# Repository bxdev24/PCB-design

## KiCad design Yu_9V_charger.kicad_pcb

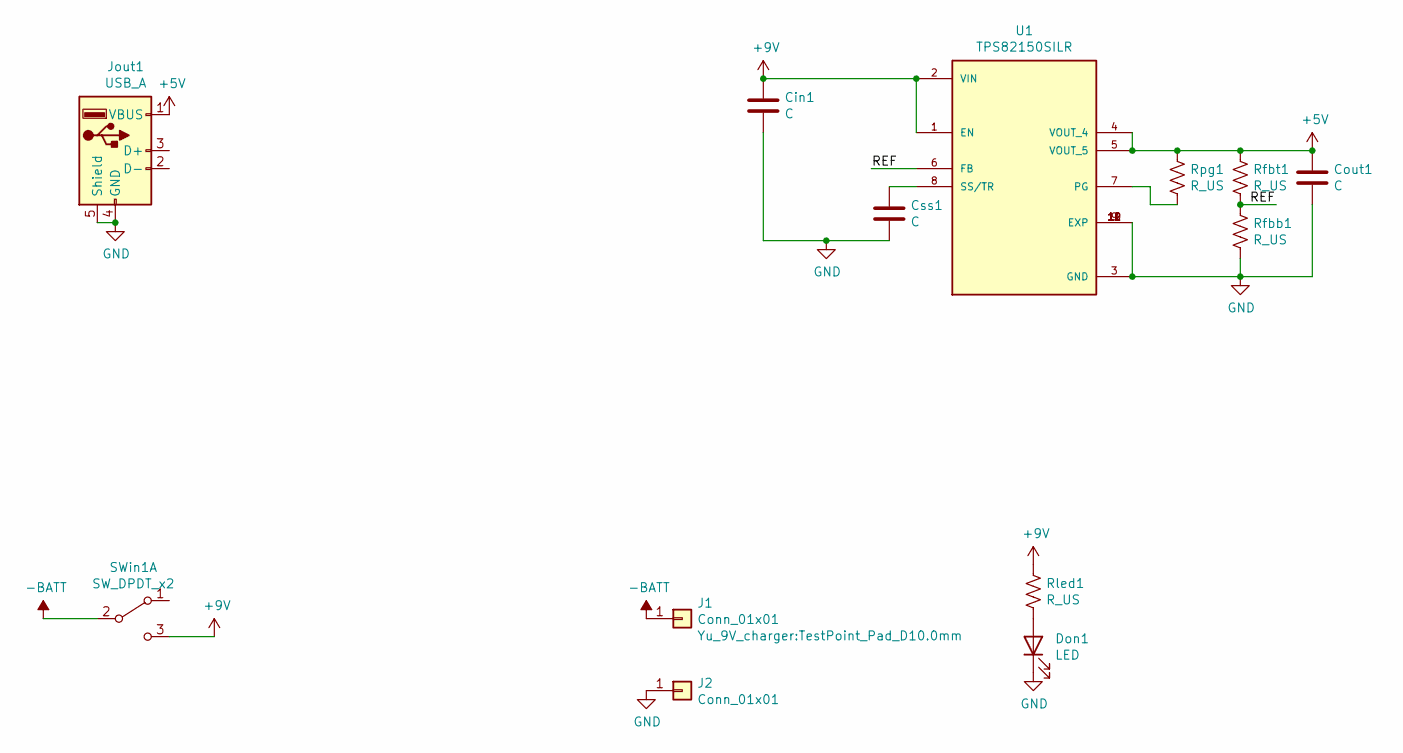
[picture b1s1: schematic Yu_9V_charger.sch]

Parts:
Cin1: C; C_1206_3216Metric
Cout1: C; C_1206_3216Metric
Css1: C; C_1206_3216Metric
Don1: LED; LED_1206_3216Metric
J1, J2: Conn_01x01; TestPoint_Pad_D10.0mm
Jout1: USB_A; USB_A_Molex_67643_Horizontal
Rfbb1: R_US; R_1206_3216Metric
Rfbt1: R_US; R_1206_3216Metric
Rled1: R_US; R_1206_3216Metric
Rpg1: R_US; R_1206_3216Metric
SWin1: SW_DPDT_x2; SW_SPDT_CK-JS102011SAQN
U1: TPS82150SILR; CONV_TPS82150SILR

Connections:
+5V: Cout1.1, Jout1.1 (VBUS), Rfbt1.1, Rpg1.1, U1.4 (VOUT_4), U1.5 (VOUT_5)
+9V: Cin1.1, Rled1.1, SWin1.3 (C), U1.1 (EN), U1.2 (VIN)
-BATT: J1.1, SWin1.2 (B)
/REF: Rfbb1.1, Rfbt1.2, U1.6 (FB)
GND: Cin1.2, Cout1.2, Css1.2, Don1.1 (K), J2.1, Jout1.4 (GND), Jout1.5 (Shield), Rfbb1.2, U1.3 (GND), U1.9 (EXP), U1.10 (EXP), U1.11 (EXP), U1.12 (EXP)
unnamed: Css1.1, U1.8 (SS/TR)
unnamed: Don1.2 (A), Rled1.2
unnamed: Rpg1.2, U1.7 (PG)

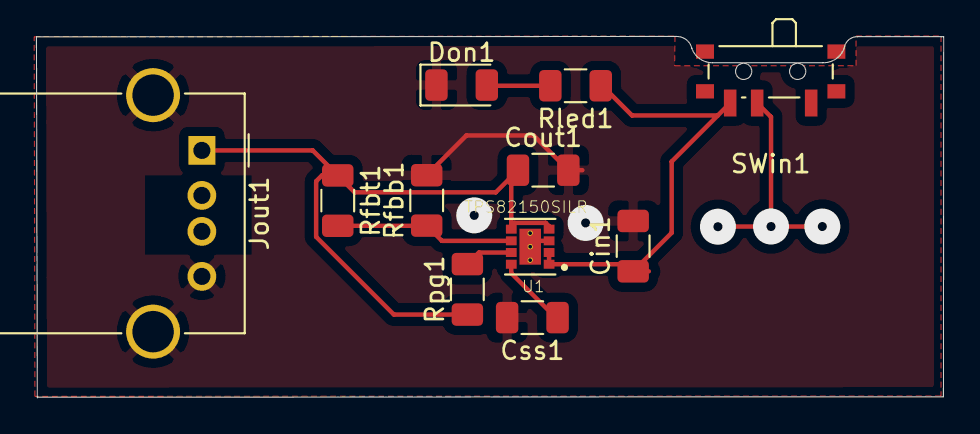
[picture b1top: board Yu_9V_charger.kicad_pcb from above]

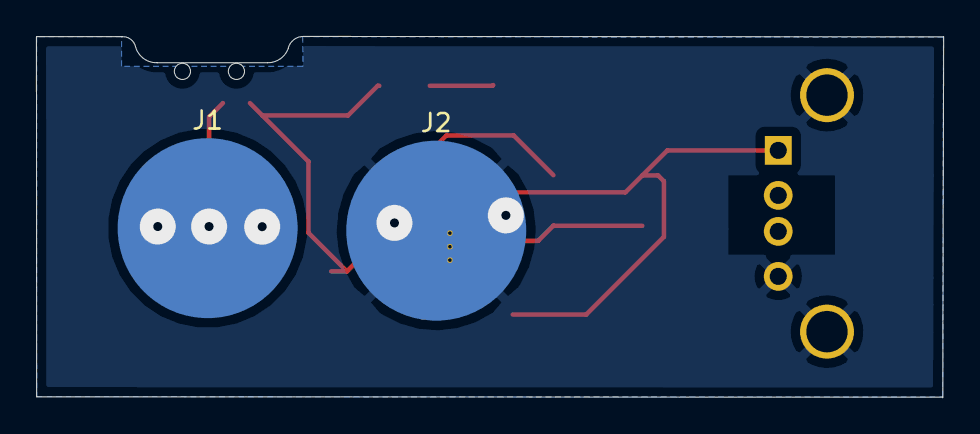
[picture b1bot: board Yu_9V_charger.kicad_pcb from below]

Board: 2 copper layers, 50.4 x 20.1 mm, 13 parts (2 on the bottom side), 8 nets.

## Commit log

2021-03-23 final
